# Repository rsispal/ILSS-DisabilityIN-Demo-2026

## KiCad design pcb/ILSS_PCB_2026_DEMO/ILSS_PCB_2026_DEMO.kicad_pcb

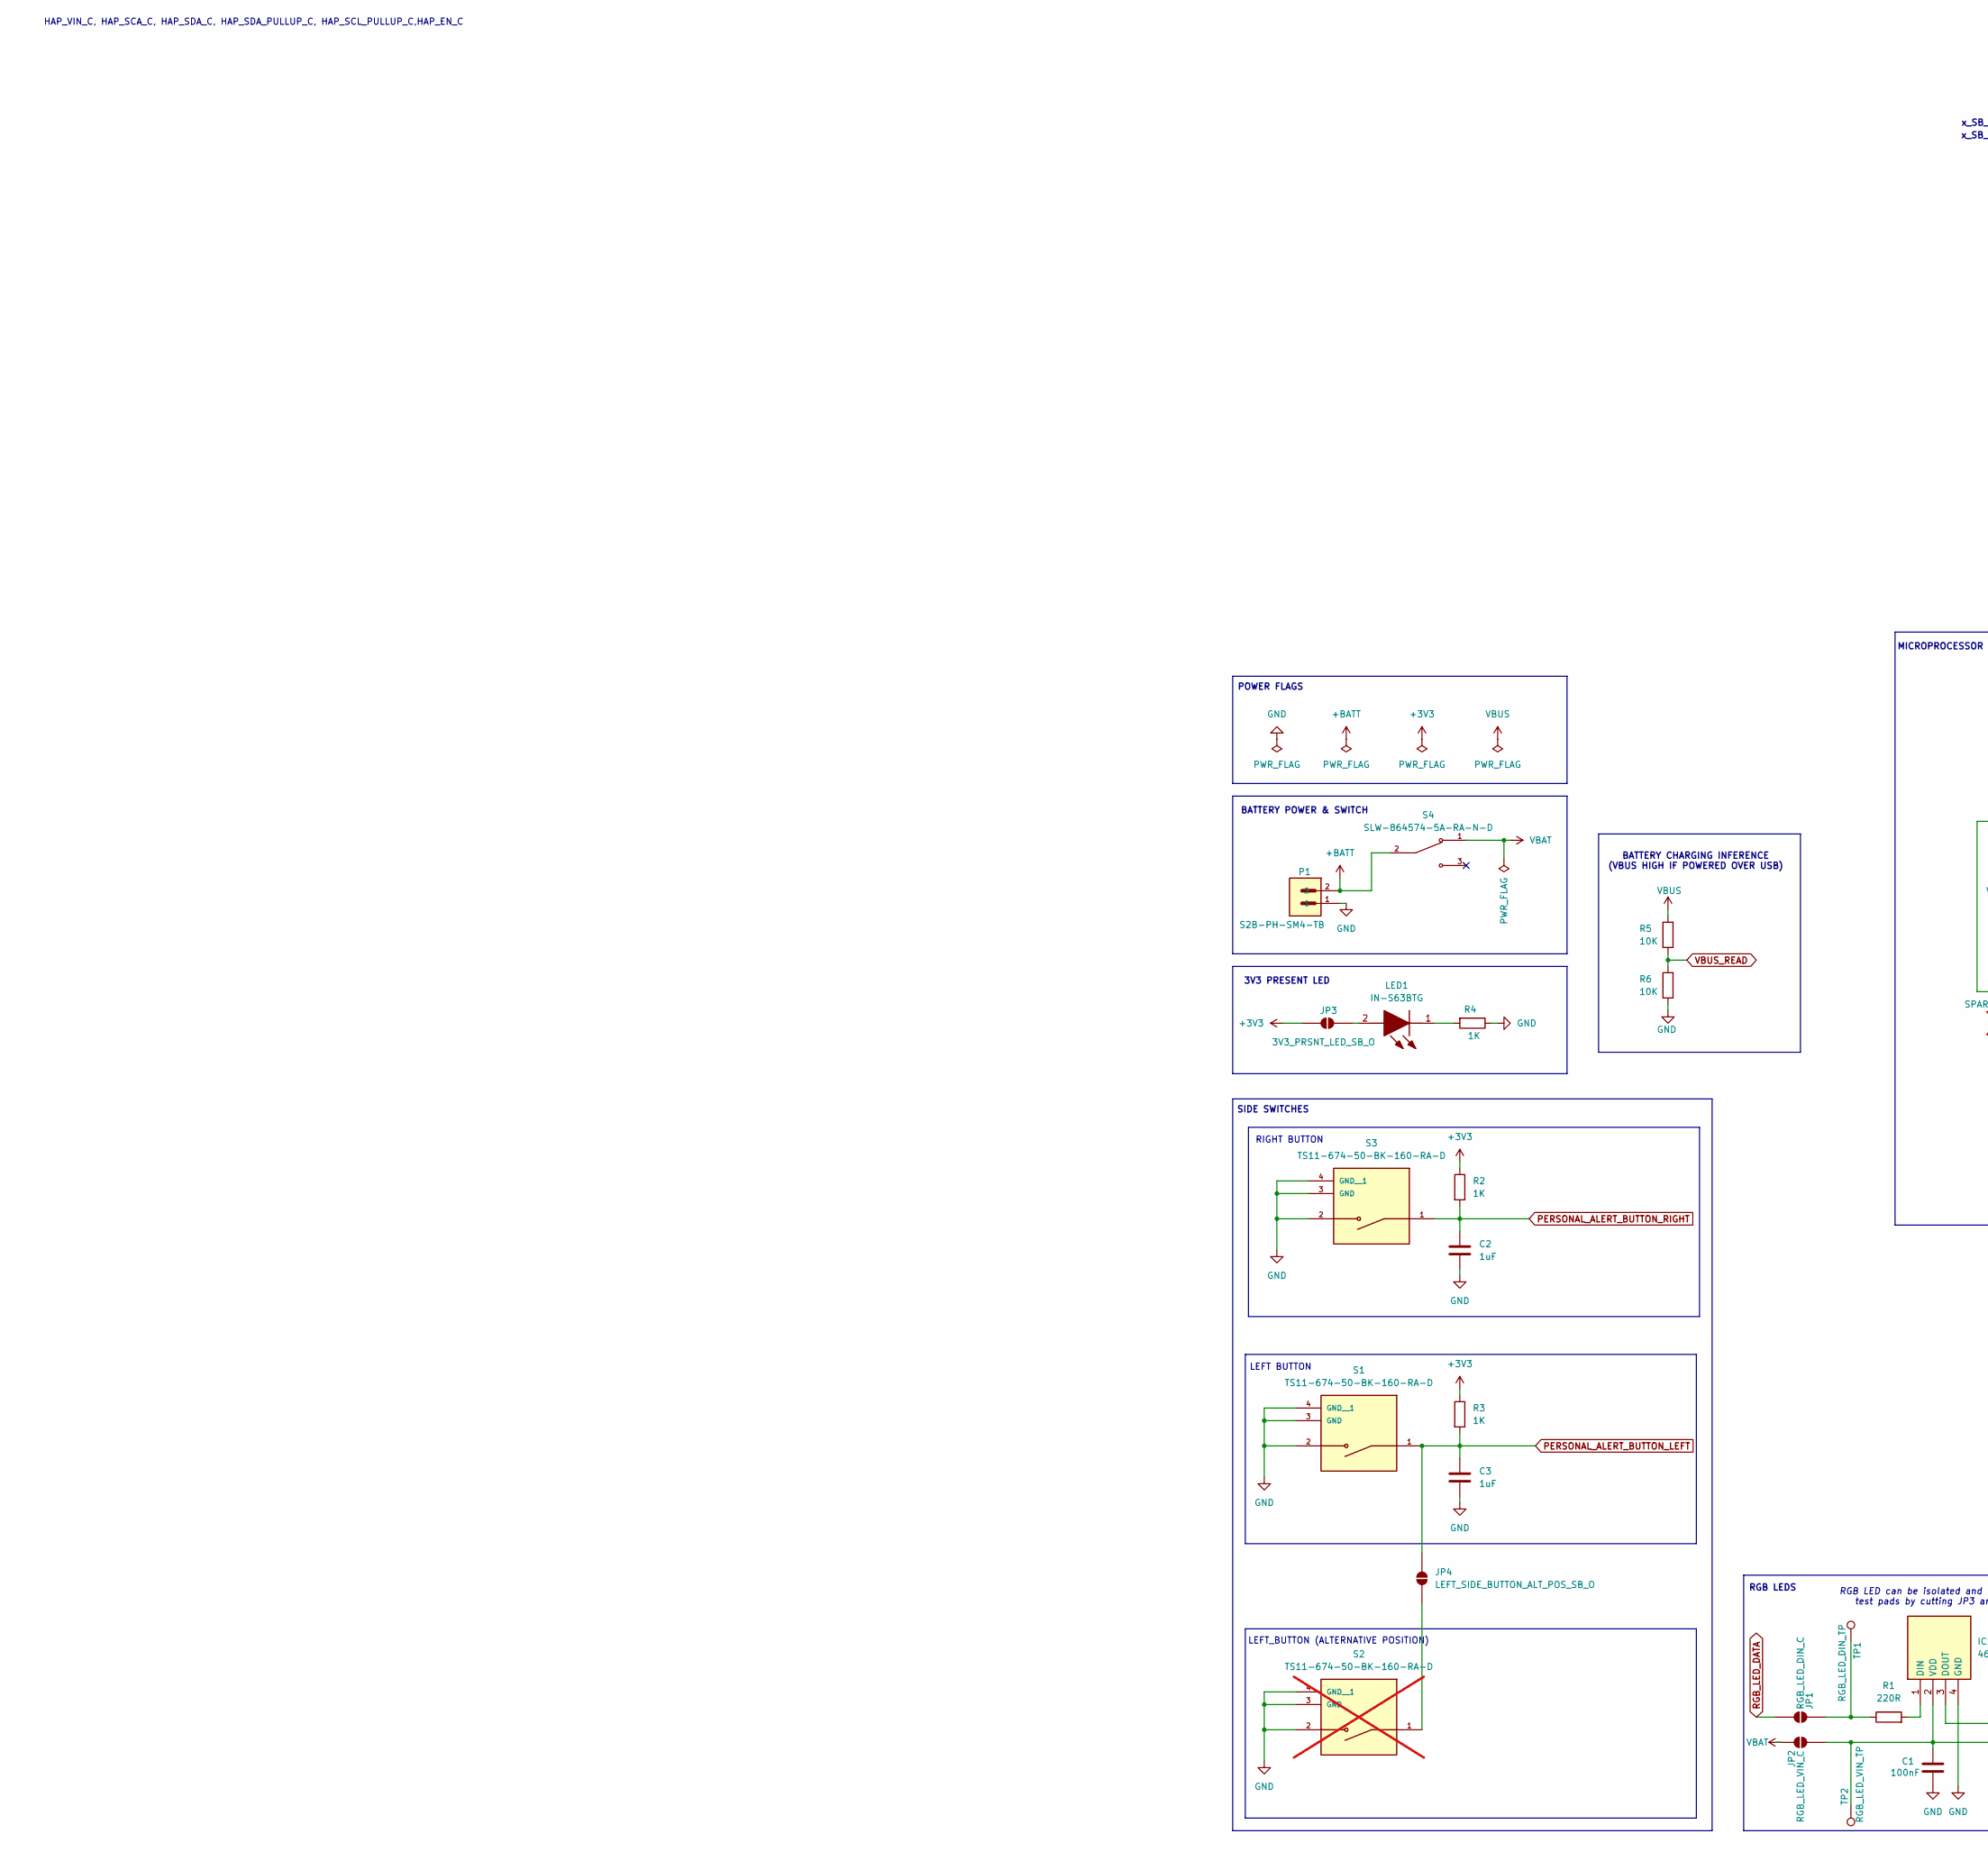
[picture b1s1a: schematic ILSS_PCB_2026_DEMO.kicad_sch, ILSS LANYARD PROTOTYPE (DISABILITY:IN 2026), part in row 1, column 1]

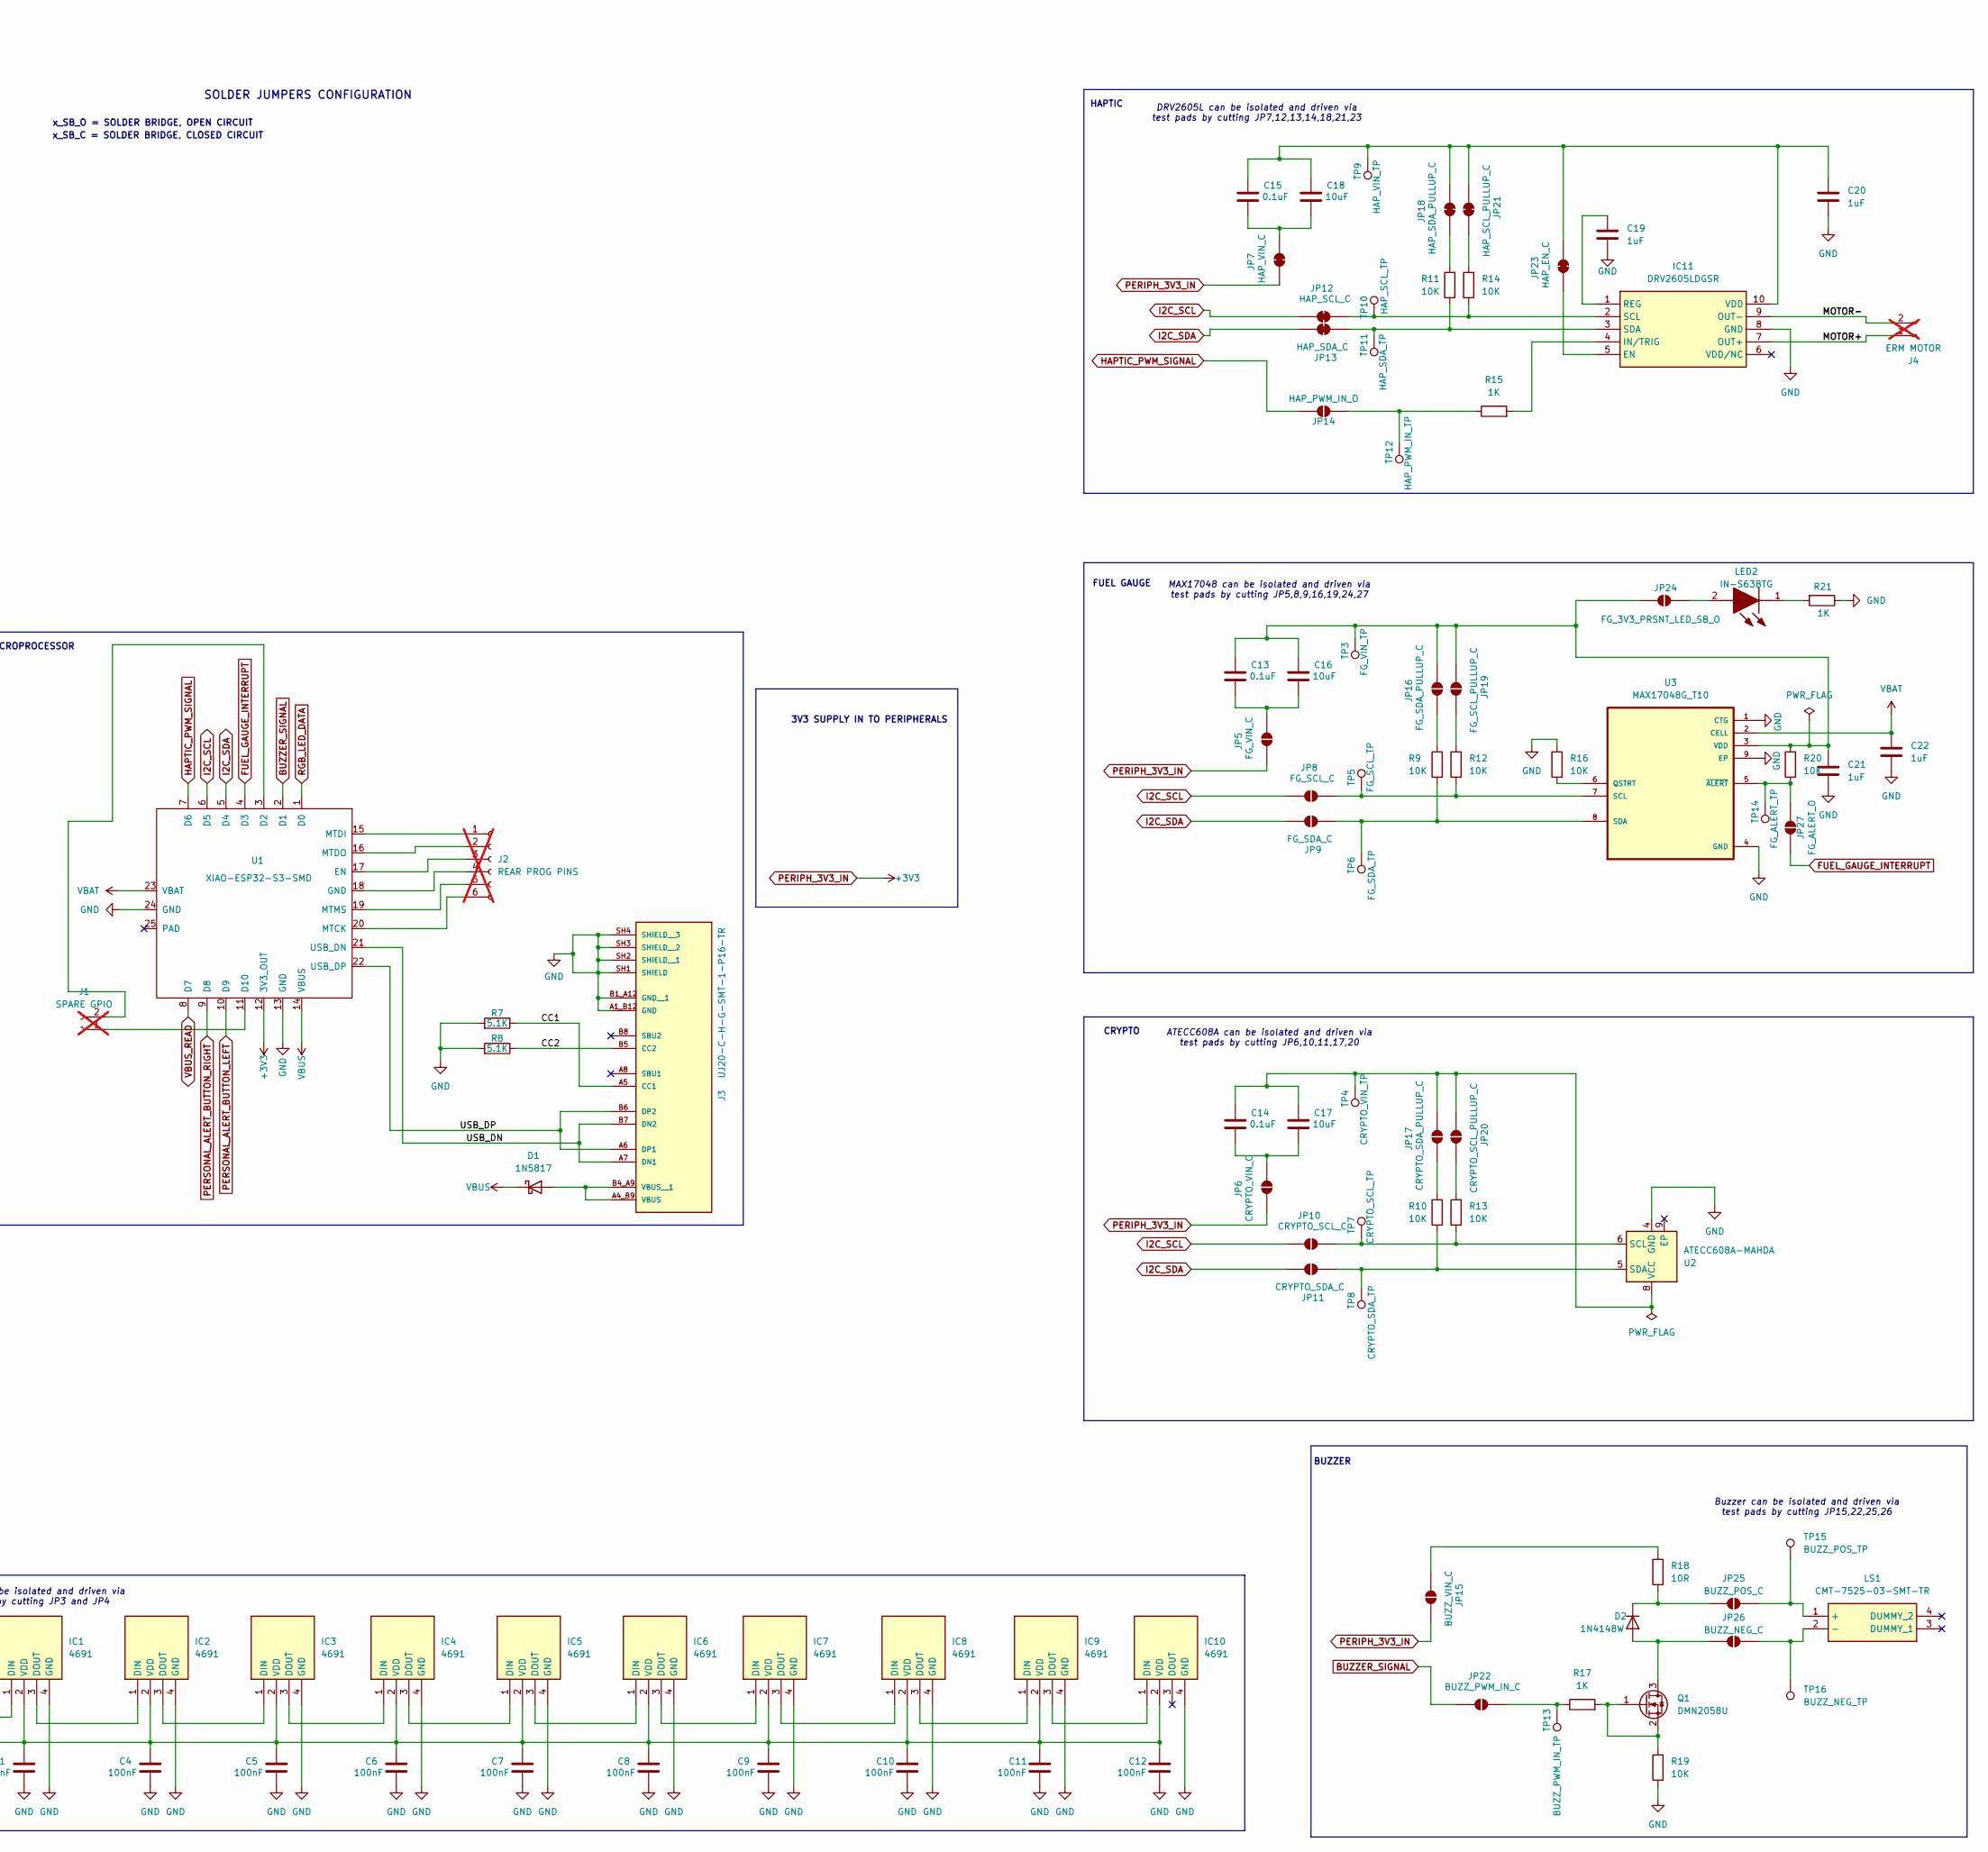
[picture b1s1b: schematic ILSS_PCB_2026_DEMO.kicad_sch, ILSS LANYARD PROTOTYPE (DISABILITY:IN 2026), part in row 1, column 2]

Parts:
C1, C4, C5, C6, C7, C8, C9, C10, C11, C12: 100nF; C_0603_1608Metric_Pad1.08x0.95mm_HandSolder
C2, C3, C19, C20, C21, C22: 1uF; C_0603_1608Metric_Pad1.08x0.95mm_HandSolder
C13, C14, C15: 0.1uF; C_0603_1608Metric_Pad1.08x0.95mm_HandSolder
C16, C17, C18: 10uF; C_0603_1608Metric_Pad1.08x0.95mm_HandSolder
D1: 1N5817; D_SOD-123
D2: 1N4148W; D_SOD-123
IC1, IC2, IC3, IC4, IC5, IC6, IC7, IC8, IC9, IC10: 4691; ADAFRUIT_SK6812_SIDE_4691; Mouser Part Number 485-4691
IC11: DRV2605LDGSR; SOP50P490X110-10N; Mouser Part Number 595-DRV2605LDGSR
J1: SPARE GPIO; PinHeader_1x02_P2.54mm_Vertical; not fitted
J2: REAR PROG PINS; PinHeader_1x06_P2.54mm_Vertical; not fitted
J3: UJ20-C-H-G-SMT-1-P16-TR; SAMESKY_UJ20-C-H-G-SMT-1-P16-TR; PARTREV 1.0
J4: ERM MOTOR; PinHeader_1x02_P2.54mm_Vertical; not fitted
JP1: RGB_LED_DIN_C; SolderJumper-2_P1.3mm_Open_Pad1.0x1.5mm
JP2: RGB_LED_VIN_C; SolderJumper-2_P1.3mm_Open_Pad1.0x1.5mm
JP3: 3V3_PRSNT_LED_SB_O; SolderJumper-2_P1.3mm_Open_Pad1.0x1.5mm
JP4: LEFT_SIDE_BUTTON_ALT_POS_SB_O; SolderJumper-2_P1.3mm_Open_Pad1.0x1.5mm
JP5: FG_VIN_C; SolderJumper-2_P1.3mm_Open_Pad1.0x1.5mm
JP6: CRYPTO_VIN_C; SolderJumper-2_P1.3mm_Open_Pad1.0x1.5mm
JP7: HAP_VIN_C; SolderJumper-2_P1.3mm_Open_Pad1.0x1.5mm
JP8: FG_SCL_C; SolderJumper-2_P1.3mm_Open_Pad1.0x1.5mm
JP9: FG_SDA_C; SolderJumper-2_P1.3mm_Open_Pad1.0x1.5mm
JP10: CRYPTO_SCL_C; SolderJumper-2_P1.3mm_Open_Pad1.0x1.5mm
JP11: CRYPTO_SDA_C; SolderJumper-2_P1.3mm_Open_Pad1.0x1.5mm
JP12: HAP_SCL_C; SolderJumper-2_P1.3mm_Open_Pad1.0x1.5mm
JP13: HAP_SDA_C; SolderJumper-2_P1.3mm_Open_Pad1.0x1.5mm
JP14: HAP_PWM_IN_O; SolderJumper-2_P1.3mm_Open_Pad1.0x1.5mm
JP15: BUZZ_VIN_C; SolderJumper-2_P1.3mm_Open_Pad1.0x1.5mm
JP16: FG_SDA_PULLUP_C; SolderJumper-2_P1.3mm_Open_Pad1.0x1.5mm
JP17: CRYPTO_SDA_PULLUP_C; SolderJumper-2_P1.3mm_Open_Pad1.0x1.5mm
JP18: HAP_SDA_PULLUP_C; SolderJumper-2_P1.3mm_Open_Pad1.0x1.5mm
JP19: FG_SCL_PULLUP_C; SolderJumper-2_P1.3mm_Open_Pad1.0x1.5mm
JP20: CRYPTO_SCL_PULLUP_C; SolderJumper-2_P1.3mm_Open_Pad1.0x1.5mm
JP21: HAP_SCL_PULLUP_C; SolderJumper-2_P1.3mm_Open_Pad1.0x1.5mm
JP22: BUZZ_PWM_IN_C; SolderJumper-2_P1.3mm_Open_Pad1.0x1.5mm
JP23: HAP_EN_C; SolderJumper-2_P1.3mm_Open_Pad1.0x1.5mm
JP24: FG_3V3_PRSNT_LED_SB_O; SolderJumper-2_P1.3mm_Open_Pad1.0x1.5mm
JP25: BUZZ_POS_C; SolderJumper-2_P1.3mm_Open_Pad1.0x1.5mm
JP26: BUZZ_NEG_C; SolderJumper-2_P1.3mm_Open_Pad1.0x1.5mm
JP27: FG_ALERT_O; SolderJumper-2_P1.3mm_Open_Pad1.0x1.5mm
LED1, LED2: IN-S63BTG; LEDC1608X55N; Mouser Part Number 743-IN-S63BTG
LS1: CMT-7525-03-SMT-TR; CMT752503SMTTR; Mouser Part Number 179-CMT-7525-03SMTTR
P1: S2B-PH-SM4-TB; JST_S2B-PH-SM4-TB
Q1: DMN2058U; SOT-23
R1: 220R; R_0603_1608Metric_Pad0.98x0.95mm_HandSolder
R2, R3, R4, R15, R17, R21: 1K; R_0603_1608Metric_Pad0.98x0.95mm_HandSolder
R5, R6, R9, R10, R11, R12, R13, R14, R16, R19, R20: 10K; R_0603_1608Metric_Pad0.98x0.95mm_HandSolder
R7, R8: 5.1K; R_0603_1608Metric_Pad0.98x0.95mm_HandSolder
R18: 10R; R_0603_1608Metric_Pad0.98x0.95mm_HandSolder
S1, S3: TS11-674-50-BK-160-RA-D; SW_TS11-674-50-BK-160-RA-D; PARTREV 1.01
S2: TS11-674-50-BK-160-RA-D; SW_TS11-674-50-BK-160-RA-D; PARTREV 1.01; not fitted
S4: SLW-864574-5A-RA-N-D; SW_SLW-864574-5A-RA-N-D; PARTREV 1.01
TP1: RGB_LED_DIN_TP; TestPoint_Pad_D2.0mm
TP2: RGB_LED_VIN_TP; TestPoint_Pad_D2.0mm
TP3: FG_VIN_TP; TestPoint_Pad_D2.0mm
TP4: CRYPTO_VIN_TP; TestPoint_Pad_D2.0mm
TP5: FG_SCL_TP; TestPoint_Pad_D2.0mm
TP6: FG_SDA_TP; TestPoint_Pad_D2.0mm
TP7: CRYPTO_SCL_TP; TestPoint_Pad_D2.0mm
TP8: CRYPTO_SDA_TP; TestPoint_Pad_D2.0mm
TP9: HAP_VIN_TP; TestPoint_Pad_D2.0mm
TP10: HAP_SCL_TP; TestPoint_Pad_D2.0mm
TP11: HAP_SDA_TP; TestPoint_Pad_D2.0mm
TP12: HAP_PWM_IN_TP; TestPoint_Pad_D2.0mm
TP13: BUZZ_PWM_IN_TP; TestPoint_Pad_D2.0mm
TP14: FG_ALERT_TP; TestPoint_Pad_D2.0mm
TP15: BUZZ_POS_TP; TestPoint_Pad_D2.0mm
TP16: BUZZ_NEG_TP; TestPoint_Pad_D2.0mm
U1: XIAO-ESP32-S3-SMD
U2: ATECC608A-MAHDA; DFN-8-1EP_3x2mm_P0.5mm_EP1.3x1.5mm
U3: MAX17048G_T10; SON50P200X200X80-9N

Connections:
+BATT: P1.2, S4.2
/CC1: J3.A5 (CC1), R7.1
/CC2: J3.B5 (CC2), R8.1
/MOTOR+: IC11.7 (OUT+), J4.1
/MOTOR-: IC11.9 (OUT-), J4.2
/USB_DN: J3.A7 (DN1), J3.B7 (DN2), U1.21 (USB_DN)
/USB_DP: J3.A6 (DP1), J3.B6 (DP2), U1.22 (USB_DP)
BUZZER_SIGNAL: JP22.2 (B), U1.2 (D1)
FUEL_GAUGE_INTERRUPT: JP27.1 (A), U1.4 (D3)
GND: C1.2, C2.2, C3.2, C4.2, C5.2, C6.2, C7.2, C8.2, C9.2, C10.2, C11.2, C12.2, C19.2, C20.1, C21.1, C22.1, IC1.4 (GND), IC2.4 (GND), IC3.4 (GND), IC4.4 (GND), IC5.4 (GND), IC6.4 (GND), IC7.4 (GND), IC8.4 (GND), IC9.4 (GND), IC10.4 (GND), IC11.8 (GND), J3.A1_B12 (GND), J3.B1_A12 (GND__1), J3.SH1 (SHIELD), J3.SH2 (SHIELD__1), J3.SH3 (SHIELD__2), J3.SH4 (SHIELD__3), P1.1, R4.1, R6.1, R7.2, R8.2, R16.2, R19.1, R21.1, S1.2, S1.3 (GND), S1.4 (GND__1), S2.2, S2.3 (GND), S2.4 (GND__1), S3.2, S3.3 (GND), S3.4 (GND__1), U1.13 (GND), U1.24 (GND), U2.4 (GND), U3.1 (CTG), U3.4 (GND), U3.9 (EP)
HAPTIC_PWM_SIGNAL: JP14.2 (B), U1.7 (D6)
I2C_SCL: JP8.2 (B), JP10.2 (B), JP12.2 (B), U1.6 (D5)
I2C_SDA: JP9.1 (A), JP11.1 (A), JP13.1 (A), U1.5 (D4)
unnamed: D1.2 (A), J3.A4_B9 (VBUS), J3.B4_A9 (VBUS__1)
unnamed: D2.2 (A), JP26.1 (A), Q1.3 (D)
unnamed: D2.1 (K), JP25.1 (A), R18.1
unnamed: IC1.1 (DIN), R1.2
unnamed: IC1.3 (DOUT), IC2.1 (DIN)
unnamed: C1.1, C4.1, C5.1, C6.1, C7.1, C8.1, C9.1, C10.1, C11.1, C12.1, IC1.2 (VDD), IC2.2 (VDD), IC3.2 (VDD), IC4.2 (VDD), IC5.2 (VDD), IC6.2 (VDD), IC7.2 (VDD), IC8.2 (VDD), IC9.2 (VDD), IC10.2 (VDD), JP2.2 (B), TP2.1 (1_1)
unnamed: IC2.3 (DOUT), IC3.1 (DIN)
unnamed: IC3.3 (DOUT), IC4.1 (DIN)
unnamed: IC4.3 (DOUT), IC5.1 (DIN)
unnamed: IC5.3 (DOUT), IC6.1 (DIN)
unnamed: IC6.3 (DOUT), IC7.1 (DIN)
unnamed: IC7.3 (DOUT), IC8.1 (DIN)
unnamed: IC8.3 (DOUT), IC9.1 (DIN)
unnamed: IC9.3 (DOUT), IC10.1 (DIN)
unnamed: IC11.5 (EN), JP23.2 (B)
unnamed: IC11.4 (IN/TRIG), R15.2
unnamed: C19.1, IC11.1 (REG)
unnamed: IC11.2 (SCL), JP12.1 (A), R14.1, TP10.1 (1_1)
unnamed: IC11.3 (SDA), JP13.2 (B), R11.1, TP11.1 (1_1)
unnamed: C15.1, C18.1, C20.2, IC11.10 (VDD), JP18.1 (A), JP21.2 (B), JP23.1 (A), TP9.1 (1_1)
unnamed: J1.1, U1.11 (D10)
unnamed: J1.2, U1.3 (D2)
unnamed: J2.1, U1.15 (MTDI)
unnamed: J2.2, U1.16 (MTDO)
unnamed: J2.3, U1.17 (EN)
unnamed: J2.4, U1.18 (GND)
unnamed: J2.5, U1.19 (MTMS)
unnamed: J2.6, U1.20 (MTCK)
unnamed: JP1.1 (A), R1.1, TP1.1 (1_1)
unnamed: JP3.2 (B), LED1.2 (A)
unnamed: JP4.1 (A), S2.1
unnamed: C13.2, C16.2, JP5.1 (A)
unnamed: C14.2, C17.2, JP6.1 (A)
unnamed: C15.2, C18.2, JP7.1 (A)
unnamed: JP8.1 (A), R12.1, TP5.1 (1_1), U3.7 (SCL)
unnamed: JP9.2 (B), R9.1, TP6.1 (1_1), U3.8 (SDA)
unnamed: JP10.1 (A), R13.1, TP7.1 (1_1), U2.6 (SCL)
unnamed: JP11.2 (B), R10.1, TP8.1 (1_1), U2.5 (SDA)
unnamed: JP14.1 (A), R15.1, TP12.1 (1_1)
unnamed: JP15.2 (B), R18.2
unnamed: C13.1, C16.1, C21.2, JP16.1 (A), JP19.2 (B), JP24.1 (A), R20.2, TP3.1 (1_1), U3.3 (VDD)
unnamed: JP16.2 (B), R9.2
unnamed: C14.1, C17.1, JP17.1 (A), JP20.2 (B), TP4.1 (1_1), U2.8 (VCC)
unnamed: JP17.2 (B), R10.2
unnamed: JP18.2 (B), R11.2
unnamed: JP19.1 (A), R12.2
unnamed: JP20.1 (A), R13.2
unnamed: JP21.1 (A), R14.2
unnamed: JP22.1 (A), R17.1, TP13.1 (1_1)
unnamed: JP24.2 (B), LED2.2 (A)
unnamed: JP25.2 (B), LS1.1 (+), TP15.1 (1_1)
unnamed: JP26.2 (B), LS1.2 (-), TP16.1 (1_1)
unnamed: JP27.2 (B), R20.1, TP14.1 (1_1), U3.5 (~ALERT)
unnamed: LED1.1 (K), R4.2
unnamed: LED2.1 (K), R21.2
unnamed: Q1.1 (G), Q1.2 (S), R17.2, R19.2
unnamed: R16.1, U3.6 (QSTRT)
PERIPH_3V3_IN: JP3.1 (A), JP5.2 (B), JP6.2 (B), JP7.2 (B), JP15.1 (A), R2.1, R3.1, U1.12 (3V3_OUT)
PERSONAL_ALERT_BUTTON_LEFT: C3.1, JP4.2 (B), R3.2, S1.1, U1.10 (D9)
PERSONAL_ALERT_BUTTON_RIGHT: C2.1, R2.2, S3.1, U1.9 (D8)
RGB_LED_DATA: JP1.2 (B), U1.1 (D0)
VBAT: C22.2, JP2.1 (A), S4.1, U1.23 (VBAT), U3.2 (CELL)
VBUS: D1.1 (K), R5.2, U1.14 (VBUS)
VBUS_READ: R5.1, R6.2, U1.8 (D7)

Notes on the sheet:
ATECC608A can be isolated and driven via test pads by cutting JP6,10,11,17,20
3V3 SUPPLY IN TO PERIPHERALS
RGB LED can be isolated and driven via test pads by cutting JP3 and JP4
BATTERY CHARGING INFERENCE (VBUS HIGH IF POWERED OVER USB)
FUEL GAUGE
BUZZER
BATTERY POWER & SWITCH
HAPTIC
HAP_VIN_C, HAP_SCA_C, HAP_SDA_C, HAP_SDA_PULLUP_C, HAP_SCL_PULLUP_C,HAP_EN_C
DRV2605L can be isolated and driven via test pads by cutting JP7,12,13,14,18,21,23
LEFT_BUTTON (ALTERNATIVE POSITION)
SIDE SWITCHES
RIGHT BUTTON
Buzzer can be isolated and driven via test pads by cutting JP15,22,25,26
x_SB_C = SOLDER BRIDGE, CLOSED CIRCUIT
MAX17048 can be isolated and driven via test pads by cutting JP5,8,9,16,19,24,27
3V3 PRESENT LED
RGB LEDS
MICROPROCESSOR
CRYPTO
LEFT BUTTON
SOLDER JUMPERS CONFIGURATION
x_SB_O = SOLDER BRIDGE, OPEN CIRCUIT
POWER FLAGS

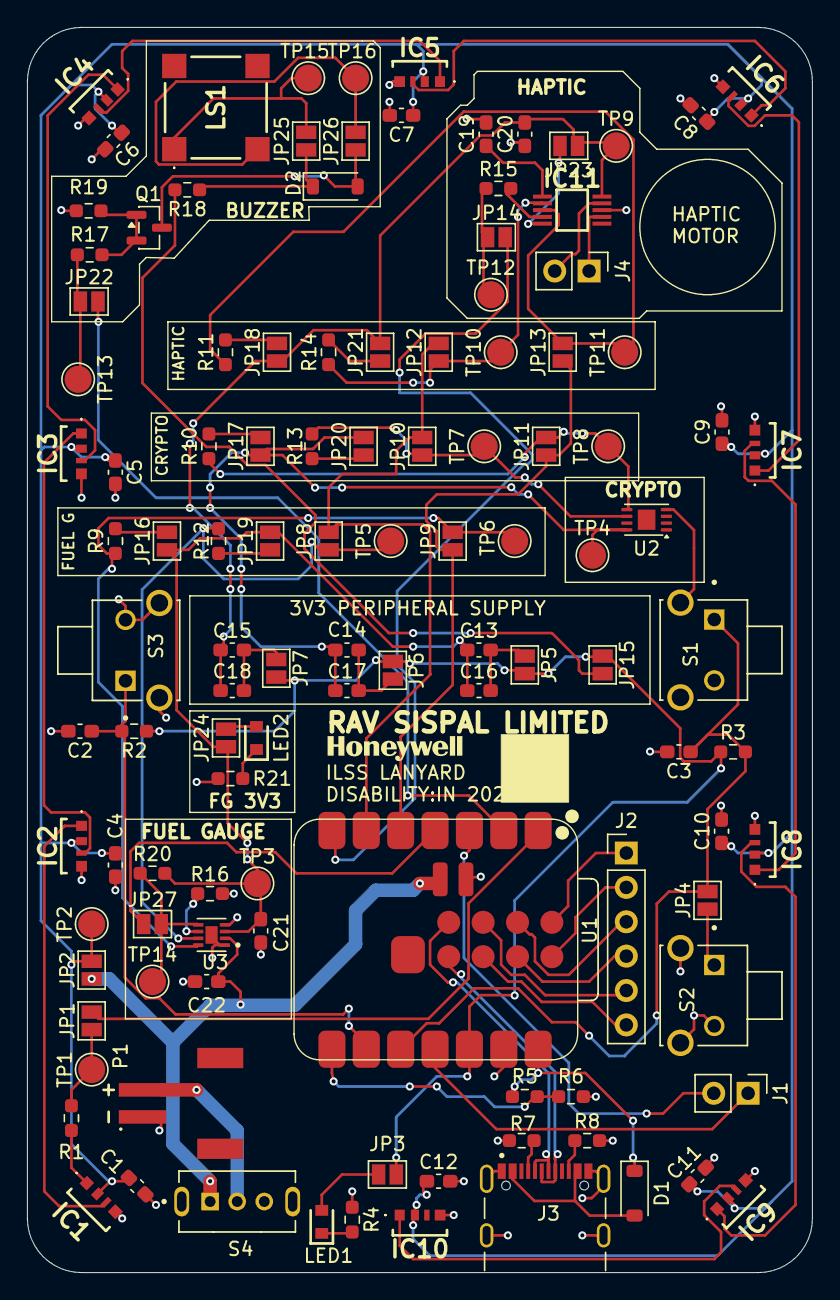
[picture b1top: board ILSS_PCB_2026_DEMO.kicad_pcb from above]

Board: 2 copper layers, 58.0 x 92.0 mm, 115 parts (0 on the bottom side), 77 nets.

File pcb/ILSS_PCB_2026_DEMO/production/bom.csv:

Designator,Footprint,Quantity,Value,LCSC Part #
"C1, C10, C11, C12, C4, C5, C6, C7, C8, C9",0603,10,100nF,
"C13, C14, C15",0603,3,0.1uF,
"C16, C17, C18",0603,3,10uF,
"C19, C2, C20, C21, C22, C3",0603,6,1uF,
D1,D_SOD-123,1,1N5817,
D2,D_SOD-123,1,1N4148W,
"IC1, IC10, IC2, IC3, IC4, IC5, IC6, IC7, IC8, IC9",ADAFRUIT_SK6812_SIDE_4691,10,4691,
IC11,SOP50P490X110-10N,1,DRV2605LDGSR,
J3,SAMESKY_UJ20-C-H-G-SMT-1-P16-TR,1,UJ20-C-H-G-SMT-1-P16-TR,
"LED1, LED2",LEDC1608X55N,2,IN-S63BTG,
LS1,CMT752503SMTTR,1,CMT-7525-03-SMT-TR,
P1,JST_S2B-PH-SM4-TB,1,S2B-PH-SM4-TB,
Q1,SOT-23,1,DMN2058U,
R1,0603,1,220R,
"R10, R11, R12, R13, R14, R16, R19, R20, R5, R6, R9",0603,11,10K,
"R15, R17, R2, R21, R3, R4",0603,6,1K,
R18,0603,1,10R,
"R7, R8",0603,2,5.1K,
"S1, S3",SW_TS11-674-50-BK-160-RA-D,2,TS11-674-50-BK-160-RA-D,
S4,SW_SLW-864574-5A-RA-N-D,1,SLW-864574-5A-RA-N-D,
TP1,TestPoint_Pad_D2.0mm,1,RGB_LED_DIN_TP,
TP10,TestPoint_Pad_D2.0mm,1,HAP_SCL_TP,
TP11,TestPoint_Pad_D2.0mm,1,HAP_SDA_TP,
TP12,TestPoint_Pad_D2.0mm,1,HAP_PWM_IN_TP,
TP13,TestPoint_Pad_D2.0mm,1,BUZZ_PWM_IN_TP,
TP14,TestPoint_Pad_D2.0mm,1,FG_ALERT_TP,
TP15,TestPoint_Pad_D2.0mm,1,BUZZ_POS_TP,
TP16,TestPoint_Pad_D2.0mm,1,BUZZ_NEG_TP,
TP2,TestPoint_Pad_D2.0mm,1,RGB_LED_VIN_TP,
TP3,TestPoint_Pad_D2.0mm,1,FG_VIN_TP,
TP4,TestPoint_Pad_D2.0mm,1,CRYPTO_VIN_TP,
TP5,TestPoint_Pad_D2.0mm,1,FG_SCL_TP,
TP6,TestPoint_Pad_D2.0mm,1,FG_SDA_TP,
TP7,TestPoint_Pad_D2.0mm,1,CRYPTO_SCL_TP,
TP8,TestPoint_Pad_D2.0mm,1,CRYPTO_SDA_TP,
TP9,TestPoint_Pad_D2.0mm,1,HAP_VIN_TP,
U1,XIAO-ESP32-S3-SMD,1,XIAO-ESP32-S3-SMD,
U2,DFN-8-1EP_3x2mm_P0.5mm_EP1.3x1.5mm,1,ATECC608A-MAHDA,
U3,SON50P200X200X80-9N,1,MAX17048G_T10,
